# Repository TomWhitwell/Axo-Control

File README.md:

# Control board for Axoloti 

This is an unnoficial knob board for the [Axoloti Core board](http://www.axoloti.com/).  It is not authorised or approved by Axoloti. 

Quick demo video: https://www.instagram.com/p/BAqbNhdjmaf/   
Another demo video: https://www.youtube.com/watch?v=lhx-O6MQIug  

## BOM  
1 x PS2/3 analogue joystick, available from [Sparkfun](https://www.sparkfun.com/products/9032) or [Cool Components](https://www.coolcomponents.co.uk/thumb-joystick.html)  

6 x 10k Potentiometers
- 9mm vertical pots 
- Linear taper, any value from 5k to 50k should be fine
- D Shaft (or whatever is suitable for your knobs)
- Try: Bourns PTV09A-4020F-B103 or Alps RK09K1130C79
- Or Alpha 9mm from [Thonk](https://www.thonk.co.uk/shop/alpha-9mm-pots/) 
- NB: If you can't find the Joystick, there is a space for a 7th pot underneath

3 x 12mm square tactile switches
- Multicomp MCDTS2-4R is the right switch, but it seems to be a fairly standard layout 
- The board also has space for standard little 6mm tactile switches
- You can get keycaps for the Omron 12mm switches:Black: KTSC-21K, White: KTSC-21I, Yellow: KTSC-21Y, Red: KTSC-21R. (

4 x 1k Resistors for LEDs (use higher values - 5k to 10k if you have ultrabright LEDs) 

4 x 3mm LEDs

4 x 11mm M3 Hex Standoffs to connect the control board to the main Axoloti Core PCB

*NB: Ignore these headers: The way the board has come out, it's impossible to solder them in, and the board is perfectly strong without them.*  2 x 2 pin Female Header 571-215297-2 to mount on the back of the Control board to provide support by connecting to pins on the X3 and X4 headers. There is no electrical connection here. 

1 x 40 pin Female Header to mount on the Axoloti core 

1 x 40 pin Male Header to mount on the Control board

## STATUS 
January 2016: Board built, works well. OSHPark project here: https://oshpark.com/shared_projects/XJm2ysZW  
Video here: https://www.instagram.com/p/BAqbNhdjmaf/   
December 2015: Design completed for Rev1 board, prototypes ordered from OSH Park. Design, BOM, Layout NOT VERIFIED. 

## LICENSE 
This project is Open Hardware  
All hardware and software design in this project is Creative Commons licensed by Tom Whitwell: CC-BY-SA: Attribution / ShareAlike.  
If you use any work in this project, you should credit me, and you must republish any changes you make under the same license.  
This license does permit commercial use of these designs, but consider getting in touch before selling anything.  
This license does not include or imply any connection to the Axoloti project by Johannes Taelman.

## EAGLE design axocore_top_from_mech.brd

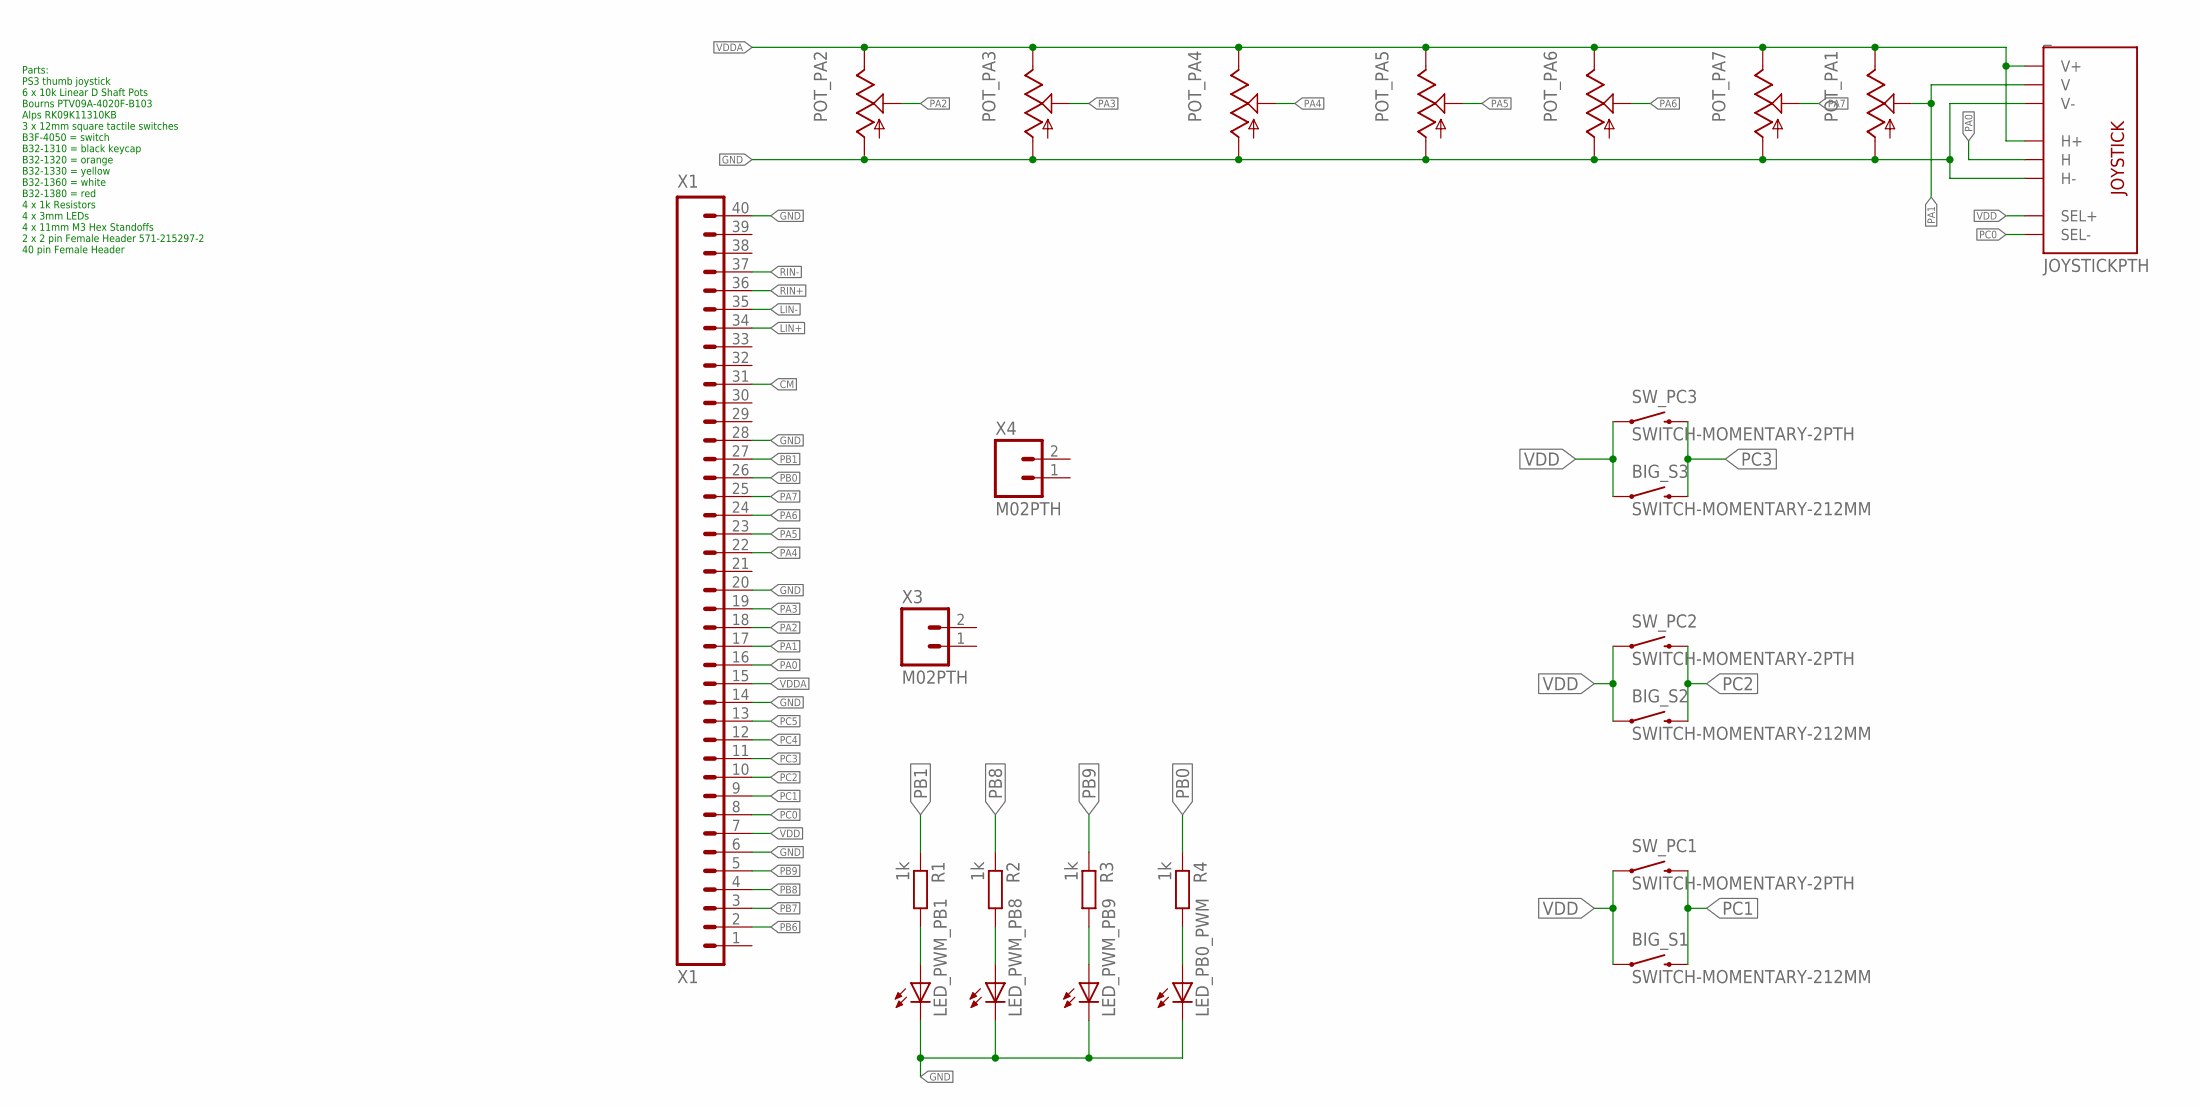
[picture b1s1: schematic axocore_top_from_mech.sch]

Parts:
BIG_S1, BIG_S2, BIG_S3: SWITCH-MOMENTARY-212MM; TACTILE-PTH-12MM
LED_PB0_PWM: LED3MM
LED_PWM_PB1, LED_PWM_PB8, LED_PWM_PB9: LED3MM
POT_PA1, POT_PA2, POT_PA3, POT_PA4, POT_PA5, POT_PA6, POT_PA7: 9MM_SNAP-IN_POT_; 9MM_SNAP-IN_POT
R1, R2, R3, R4: 1k; 7MM_RESISTOR
SW_PC1, SW_PC2, SW_PC3: SWITCH-MOMENTARY-2PTH; TACTILE-PTH
X1: X1; 1X40
X3, X4: M02PTH; 1X02
_: JOYSTICKPTH; JOYSTICK

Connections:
CM: X1.31
GND: LED_PB0_PWM.K (C), LED_PWM_PB1.K (C), LED_PWM_PB8.K (C), LED_PWM_PB9.K (C), POT_PA1.1 (A), POT_PA2.1 (A), POT_PA3.1 (A), POT_PA4.1 (A), POT_PA5.1 (A), POT_PA6.1 (A), POT_PA7.1 (A), X1.6, X1.14, X1.20, X1.28, X1.40, _.H3 (H-), _.V3 (V-)
LIN+: X1.34
LIN-: X1.35
unnamed: LED_PWM_PB1.A, R1.2
unnamed: LED_PWM_PB8.A, R2.2
unnamed: LED_PWM_PB9.A, R3.2
unnamed: LED_PB0_PWM.A, R4.2
PA0: X1.16, _.H2 (H)
PA1: POT_PA1.2 (S), X1.17, _.V2 (V)
PA2: POT_PA2.2 (S), X1.18
PA3: POT_PA3.2 (S), X1.19
PA4: POT_PA4.2 (S), X1.22
PA5: POT_PA5.2 (S), X1.23
PA6: POT_PA6.2 (S), X1.24
PA7: POT_PA7.2 (S), X1.25
PB0: R4.1, X1.26
PB1: R1.1, X1.27
PB6: X1.2
PB7: X1.3
PB8: R2.1, X1.4
PB9: R3.1, X1.5
PC0: X1.8, _.B2A (SEL-)
PC1: BIG_S1.3 (2), SW_PC1.3 (2), X1.9
PC2: BIG_S2.3 (2), SW_PC2.3 (2), X1.10
PC3: BIG_S3.3 (2), SW_PC3.3 (2), X1.11
PC4: X1.12
PC5: X1.13
RIN+: X1.36
RIN-: X1.37
VDD: BIG_S1.1, BIG_S2.1, BIG_S3.1, SW_PC1.1, SW_PC2.1, SW_PC3.1, X1.7, _.B1A (SEL+)
VDDA: POT_PA1.3 (E), POT_PA2.3 (E), POT_PA3.3 (E), POT_PA4.3 (E), POT_PA5.3 (E), POT_PA6.3 (E), POT_PA7.3 (E), X1.15, _.H1 (H+), _.V1 (V+)

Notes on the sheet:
Parts: PS3 thumb joystick 6 x 10k Linear D Shaft Pots Bourns PTV09A-4020F-B103 Alps RK09K11310KB 3 x 12mm square tactile switches B3F-4050 = switch B32-1310 = black keycap B32-1320 = orange B32-1330 = yellow B32-1360 = white B32-1380 = red 4 x 1k Resistors 4 x 3mm LEDs 4 x 11mm M3 Hex Standoffs 2 x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

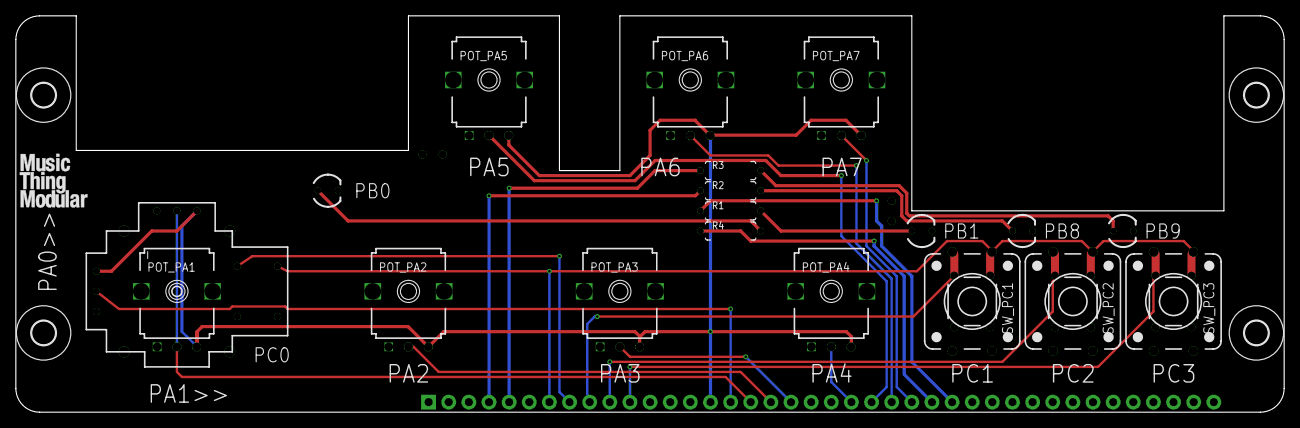
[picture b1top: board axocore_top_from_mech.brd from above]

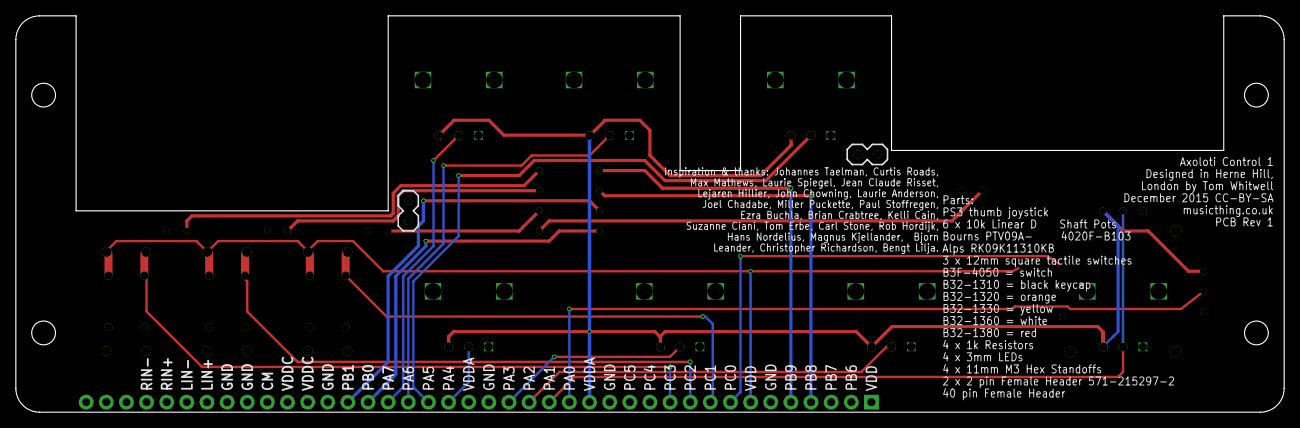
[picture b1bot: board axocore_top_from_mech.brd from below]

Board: 4 copper layers, 160.0 x 50.0 mm, 29 parts (2 on the bottom side), 23 nets.

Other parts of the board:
H1, H2, H4, H6: MOUNT-HOLE3.0; 3,0

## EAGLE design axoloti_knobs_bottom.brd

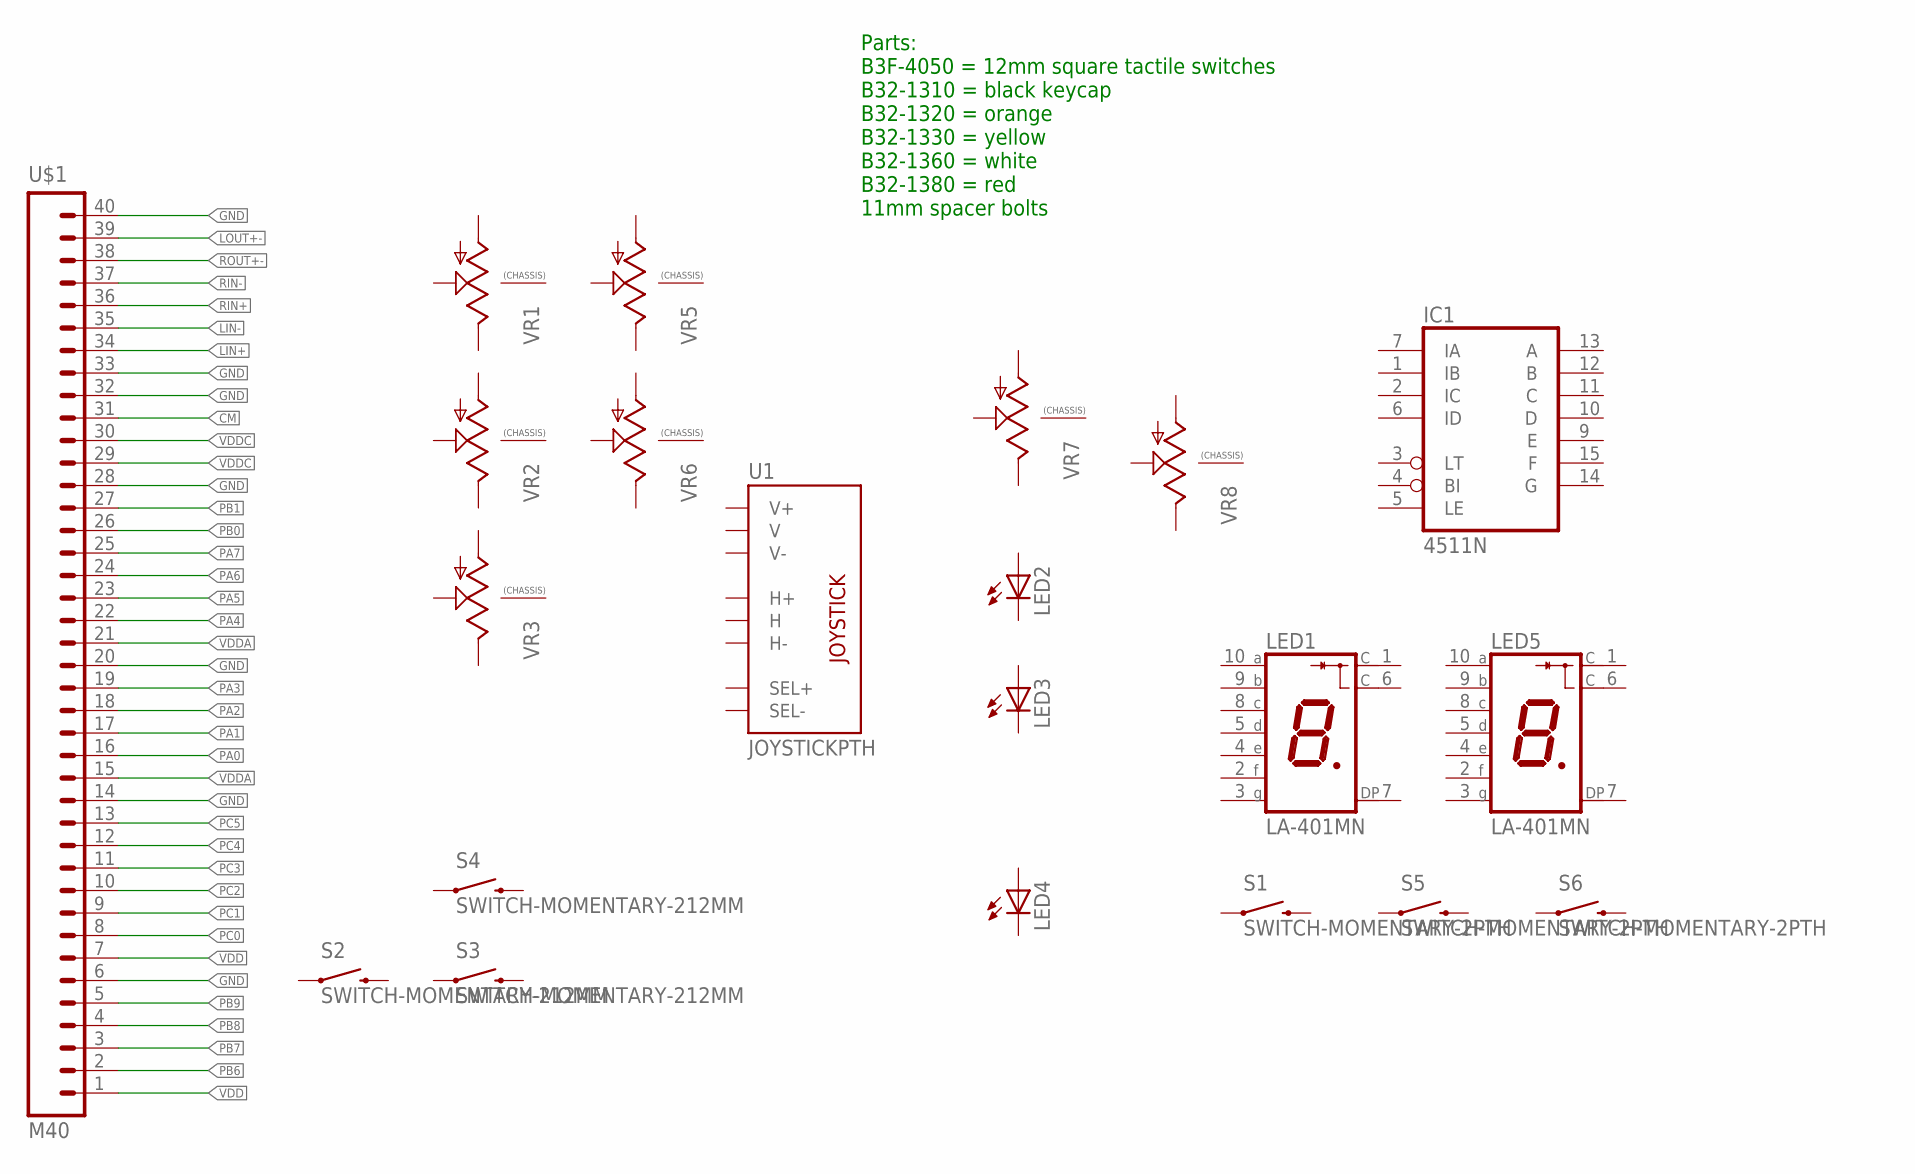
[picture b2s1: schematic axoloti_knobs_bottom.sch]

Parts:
IC1: 4511N; DIL16
LED1, LED5: LA-401MN; LA-401
LED2, LED3, LED4: LED3MM
S1, S5, S6: SWITCH-MOMENTARY-2PTH; TACTILE-PTH
S2, S3, S4: SWITCH-MOMENTARY-212MM; TACTILE-PTH-12MM
U1: JOYSTICKPTH; JOYSTICK
U$1: M40; 1X40
VR1, VR2, VR3, VR5, VR6, VR7, VR8: 9MM_SNAP-IN_POT_CHASSIS; 9MM_SNAP-IN_POT

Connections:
CM: U$1.31
GND: U$1.6, U$1.14, U$1.20, U$1.28, U$1.32, U$1.33, U$1.40
LIN+: U$1.34
LIN-: U$1.35
LOUT+-: U$1.39
PA0: U$1.16
PA1: U$1.17
PA2: U$1.18
PA3: U$1.19
PA4: U$1.22
PA5: U$1.23
PA6: U$1.24
PA7: U$1.25
PB0: U$1.26
PB1: U$1.27
PB6: U$1.2
PB7: U$1.3
PB8: U$1.4
PB9: U$1.5
PC0: U$1.8
PC1: U$1.9
PC2: U$1.10
PC3: U$1.11
PC4: U$1.12
PC5: U$1.13
RIN+: U$1.36
RIN-: U$1.37
ROUT+-: U$1.38
VDD: IC1.16 (VDD), U$1.1, U$1.7
VDDA: U$1.15, U$1.21
VDDC: U$1.29, U$1.30
VSS: IC1.8 (VSS)

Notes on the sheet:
Parts: B3F-4050 = 12mm square tactile switches B32-1310 = black keycap B32-1320 = orange B32-1330 = yellow B32-1360 = white B32-1380 = red 11mm spacer bolts

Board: 2 copper layers, 27 parts (0 on the bottom side), 4 nets, no tracks yet.

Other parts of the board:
U$2, U$3, U$4, U$5, U$6, U$7: MOUNTING_HOLE

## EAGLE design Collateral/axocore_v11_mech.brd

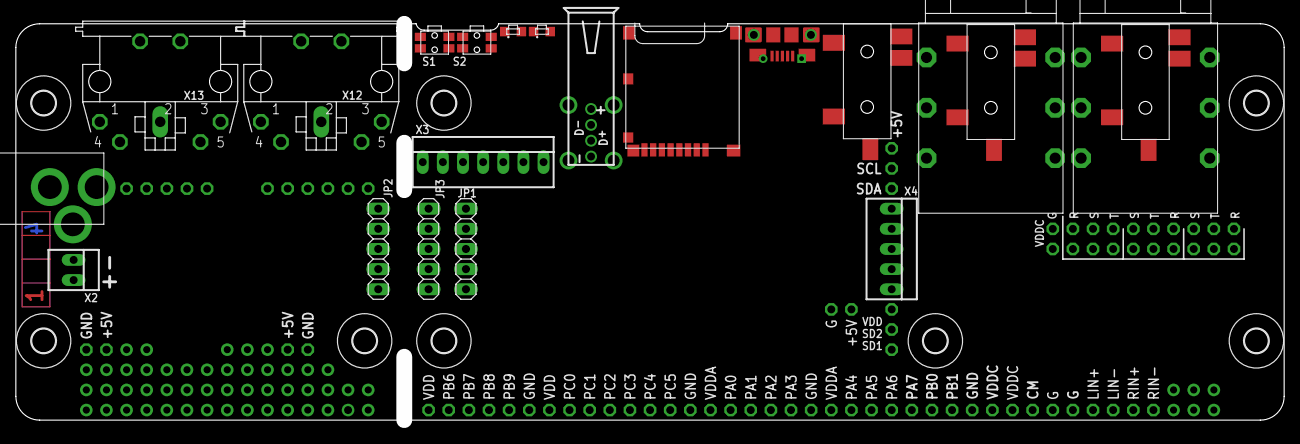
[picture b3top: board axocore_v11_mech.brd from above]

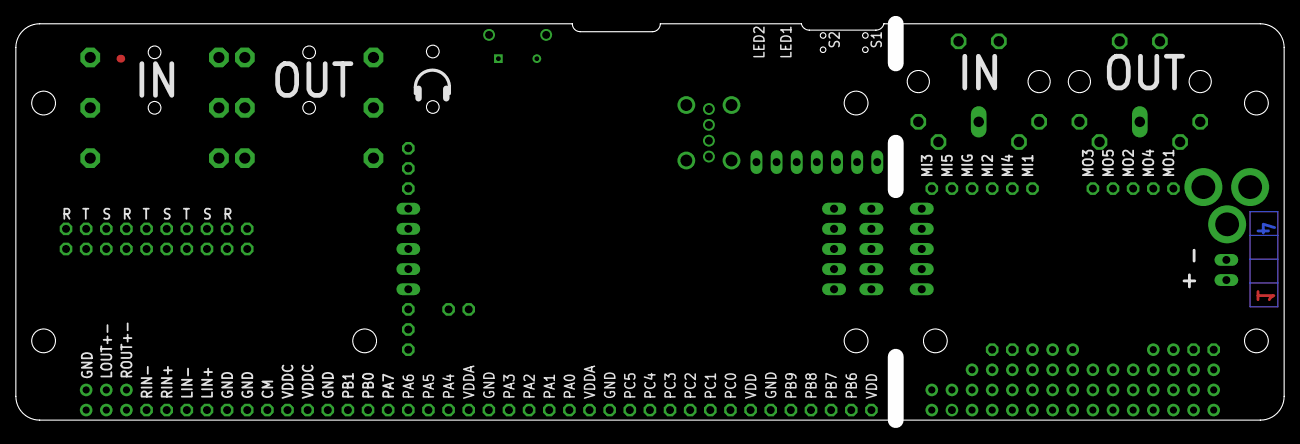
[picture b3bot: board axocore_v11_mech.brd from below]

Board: 2 copper layers, 158.0 x 50.0 mm, 109 parts (11 on the bottom side), 31 nets.

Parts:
D5: SML-A12 RED; SML-A12
D6: SML-A12 GREEN; SML-A12
H1, H2, H3, H4, H5, H6, H7, H8: MOUNT-HOLE3.0; 3,0
JP1: 1X05
JP2, JP3: NC; 1X05
S1, S2: EVQP7
TP1, TP66, TP77: VDDC; PROTOHOLE_NAMED
TP2: MI3; PROTOHOLE_NAMED
TP3: MI5; PROTOHOLE_NAMED
TP4: CM; PROTOHOLE_NAMED
TP5: MI1; PROTOHOLE_NAMED
TP6: MI4; PROTOHOLE_NAMED
TP7, TP59, TP63, TP67: G; PROTOHOLE_NAMED
TP8: MI2; PROTOHOLE_NAMED
TP9: MIG; PROTOHOLE_NAMED
TP10: MO3; PROTOHOLE_NAMED
TP11: MO1; PROTOHOLE_NAMED
TP12: MO5; PROTOHOLE_NAMED
TP13, TP57, TP58, TP60, TP61, TP62: GND; PROTOHOLE_NAMED
TP14: SD1; PROTOHOLE_NAMED
TP15: SD2; PROTOHOLE_NAMED
TP16, TP64, TP65: VDD; PROTOHOLE_NAMED
TP17: SDA; PROTOHOLE_NAMED
TP18: SCL; PROTOHOLE_NAMED
TP19, TP21, TP23, TP26, TP28, TP30: PROTOHOLE
TP20, TP29, TP36: S; PROTOHOLE_NAMED
TP22, TP27, TP34: R; PROTOHOLE_NAMED
TP24, TP25, TP32: T; PROTOHOLE_NAMED
TP31: T; PROTOHOLE
TP33: R; PROTOHOLE
TP35: S; PROTOHOLE
TP37: PA0; PROTOHOLE_NAMED
TP38: PA1; PROTOHOLE_NAMED
TP39: PA2; PROTOHOLE_NAMED
TP40: PA3; PROTOHOLE_NAMED
TP41: PA4; PROTOHOLE_NAMED
TP42: PA5; PROTOHOLE_NAMED
TP43: PA6; PROTOHOLE_NAMED
TP44: PA7; PROTOHOLE_NAMED
TP45: PB0; PROTOHOLE_NAMED
TP46: PB1; PROTOHOLE_NAMED
TP47: PB6; PROTOHOLE_NAMED
TP48: PB7; PROTOHOLE_NAMED
TP49: PB8; PROTOHOLE_NAMED
TP50: PB9; PROTOHOLE_NAMED
TP51: PC0; PROTOHOLE_NAMED
TP52: PC1; PROTOHOLE_NAMED
TP53: PC2; PROTOHOLE_NAMED
TP54: PC3; PROTOHOLE_NAMED
TP55: PC4; PROTOHOLE_NAMED
TP56: PC5; PROTOHOLE_NAMED
TP68, TP69, TP70, TP76: +5V; PROTOHOLE_NAMED
TP71, TP72: VDDA; PROTOHOLE_NAMED
TP73: MO4; PROTOHOLE_NAMED
TP74: MO2; PROTOHOLE_NAMED
TP75: LIN+; PROTOHOLE_NAMED
TP78: LIN-; PROTOHOLE_NAMED
TP79: RIN+; PROTOHOLE_NAMED
TP80: RIN-; PROTOHOLE_NAMED
USB1: FCI 73725-0110BLF; USB_A_VERTICAL_PTH
X1: 2.1MMJACKTHM; PJ-102A
X2: 22-23-2021
X3: 22-23-2071
X4: NC (22-23-2051); 22-23-2051
X5, X8: NC (35RASMT4); 35RASMT4BHNTR
X6, X7: NMJ6HFD2; JACK63
X9: 35RASMT4; 35RASMT4BHNTR
X10: ZX62D-B-5P8
X11: MOLEX_502774
X12, X13: MAB5SH

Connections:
+5V: JP2.1, JP3.1, TP68.P$1, TP69.P$1, TP70.P$1, TP76.P$1, X3.3
BLINN: TP24.P$1, TP26.P$1, X5.P3, X6.T
BLOUTP: TP31.P$1, TP32.P$1, X7.T, X8.P3
BRINN: TP27.P$1, TP28.P$1, X5.P2, X6.R
BROUTP: TP33.P$1, TP34.P$1, X7.R, X8.P2
GND: JP1.3, JP2.5, JP3.5, TP7.P$1, TP13.P$1, TP57.P$1, TP58.P$1, TP59.P$1, TP60.P$1, TP61.P$1, TP62.P$1, TP63.P$1, TP67.P$1, TP74.P$1, X1.RING, X2.1, X3.1, X4.1, X13.2, X13.PE, X13.PE@
HSHIELD: USB1.P$3, USB1.P$4
INSGND: TP29.P$1, TP30.P$1, X5.P1, X6.S
LHP: TP21.P$1, TP22.P$1, X9.P3
LIN+: TP75.P$1, TP79.P$1
MI1: TP5.P$1, X12.1
MI2: TP8.P$1, X12.2
MI3: TP2.P$1, X12.3
MIDIIN4: TP6.P$1, X12.4
MIDIIN5: TP3.P$1, X12.5
MIDIOUT4: TP73.P$1, X13.4
MIDIOUT5: TP12.P$1, X13.5
MIG: TP9.P$1, X12.PE, X12.PE@
MO1: TP11.P$1, X13.1
MO3: TP10.P$1, X13.3
MONOOUT: TP19.P$1, TP20.P$1, X9.P1
OUTSGND: TP35.P$1, TP36.P$1, X7.S, X8.P1
PB10_USART3TX: X3.2, X4.5
PG9_USART6RX: JP2.3, JP3.3
PG14_USART6TX: JP2.4, JP3.4
RHP: TP23.P$1, TP25.P$1, X9.P2
VBUSEND: JP2.2, JP3.2
VDD: JP1.1, S1.P$2, S2.P$2, TP16.P$1, TP64.P$1, TP65.P$1
VDDA1: TP71.P$1, TP72.P$1
VDDC: TP1.P$1, TP66.P$1, TP77.P$1
VINJACK1: X1.TIP, X2.2

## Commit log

2015-12-24 getting started
2015-12-26 full sized board
2015-12-26 full width board
2015-12-28 added reference board template
2015-12-28 new version on proper layout
2015-12-28 finalised layout, starting routing
2015-12-29 Completed routing
2015-12-31 Rev 1 Complete and sent to OSHPark
2016-02-23 Enlarged text on Eagle Silkscreen Layer, NOT on fancy gerber edited in Cenon
2016-06-17 Add demo patches
2016-12-29 Add schematic
2019-09-29 Minor formatting proposals

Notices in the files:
axocore_top_from_mech.brd:
December 2015 CC-BY-SA
parts and their libraries:
SparkFun-Connectors: Licensing: CC v3.0 Share-Alike You are welcome to use this library for commercial purposes.
